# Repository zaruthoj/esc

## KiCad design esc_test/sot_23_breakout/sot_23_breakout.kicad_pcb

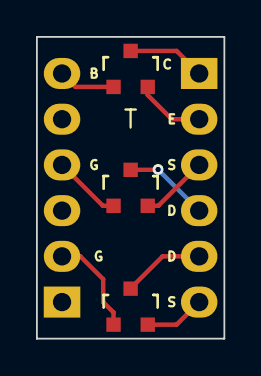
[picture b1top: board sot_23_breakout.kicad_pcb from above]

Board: 2 copper layers, 10.4 x 16.8 mm, 5 parts (0 on the bottom side), 9 nets.

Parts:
P1, P2: CONN_01X06; Pin_Header_Straight_1x06_no_outline
Q1: Q_NPN_BEC; SOT-23
Q2: P; SOT-23
Q3: N; SOT-23

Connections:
unnamed: P1.2, Q3.1
unnamed: P1.4, Q2.1
unnamed: P1.6, Q1.1
unnamed: P2.1, Q1.3
unnamed: P2.2, Q1.2
unnamed: P2.3, Q2.2
unnamed: P2.4, Q2.3
unnamed: P2.5, Q3.3
unnamed: P2.6, Q3.2

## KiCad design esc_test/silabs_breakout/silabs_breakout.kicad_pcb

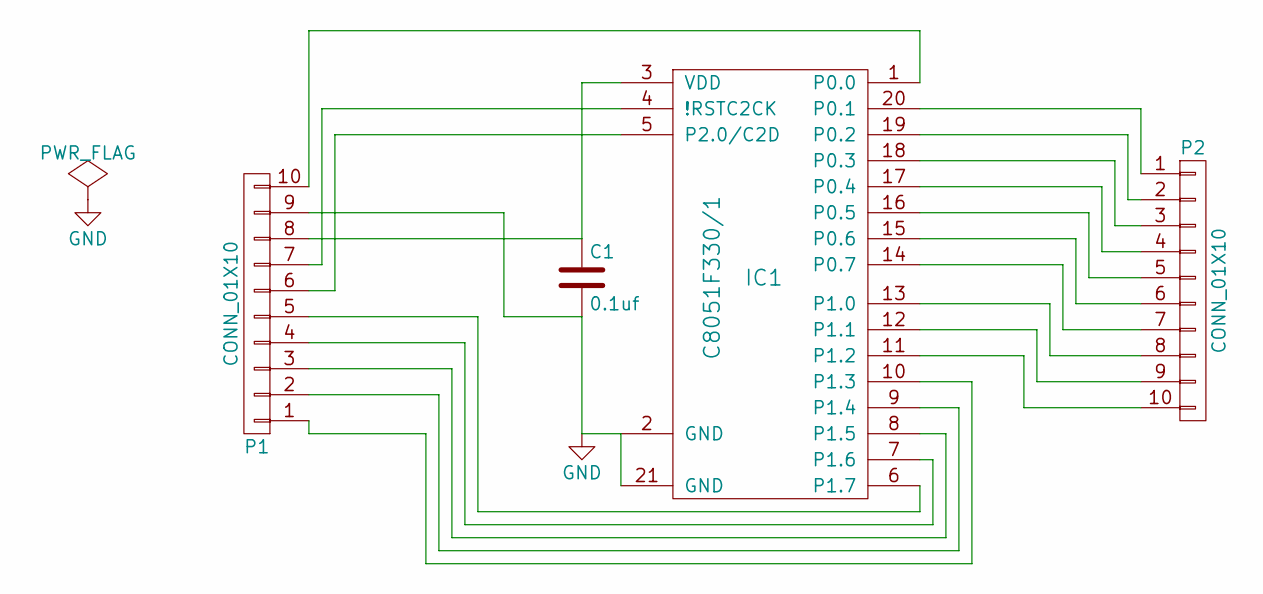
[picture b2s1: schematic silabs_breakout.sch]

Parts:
C1: 0.1uf; C_0805
IC1: C8051F330/1; QFN-20-1EP_4x4mm_Pitch0.5mm
P1, P2: CONN_01X10; Pin_Header_Straight_1x10

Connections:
GND: C1.2, IC1.2 (GND), IC1.21 (GND), P1.9
unnamed: C1.1, IC1.3 (VDD), P1.8
unnamed: IC1.1 (P0.0), P1.10
unnamed: IC1.4 (!RSTC2CK), P1.7
unnamed: IC1.5 (P2.0/C2D), P1.6
unnamed: IC1.6 (P1.7), P1.5
unnamed: IC1.7 (P1.6), P1.4
unnamed: IC1.8 (P1.5), P1.3
unnamed: IC1.9 (P1.4), P1.2
unnamed: IC1.10 (P1.3), P1.1
unnamed: IC1.11 (P1.2), P2.10
unnamed: IC1.12 (P1.1), P2.9
unnamed: IC1.13 (P1.0), P2.8
unnamed: IC1.14 (P0.7), P2.7
unnamed: IC1.15 (P0.6), P2.6
unnamed: IC1.16 (P0.5), P2.5
unnamed: IC1.17 (P0.4), P2.4
unnamed: IC1.18 (P0.3), P2.3
unnamed: IC1.19 (P0.2), P2.2
unnamed: IC1.20 (P0.1), P2.1

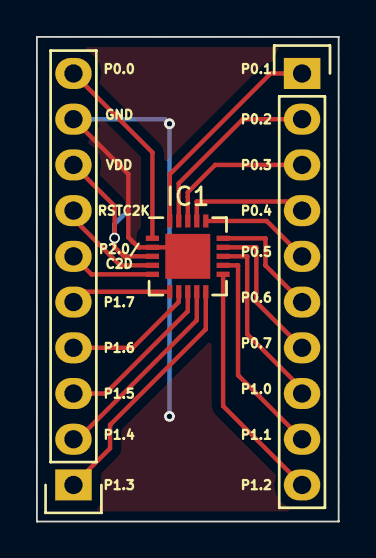
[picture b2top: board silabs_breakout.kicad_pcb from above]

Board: 2 copper layers, 16.8 x 26.9 mm, 4 parts (1 on the bottom side), 20 nets.

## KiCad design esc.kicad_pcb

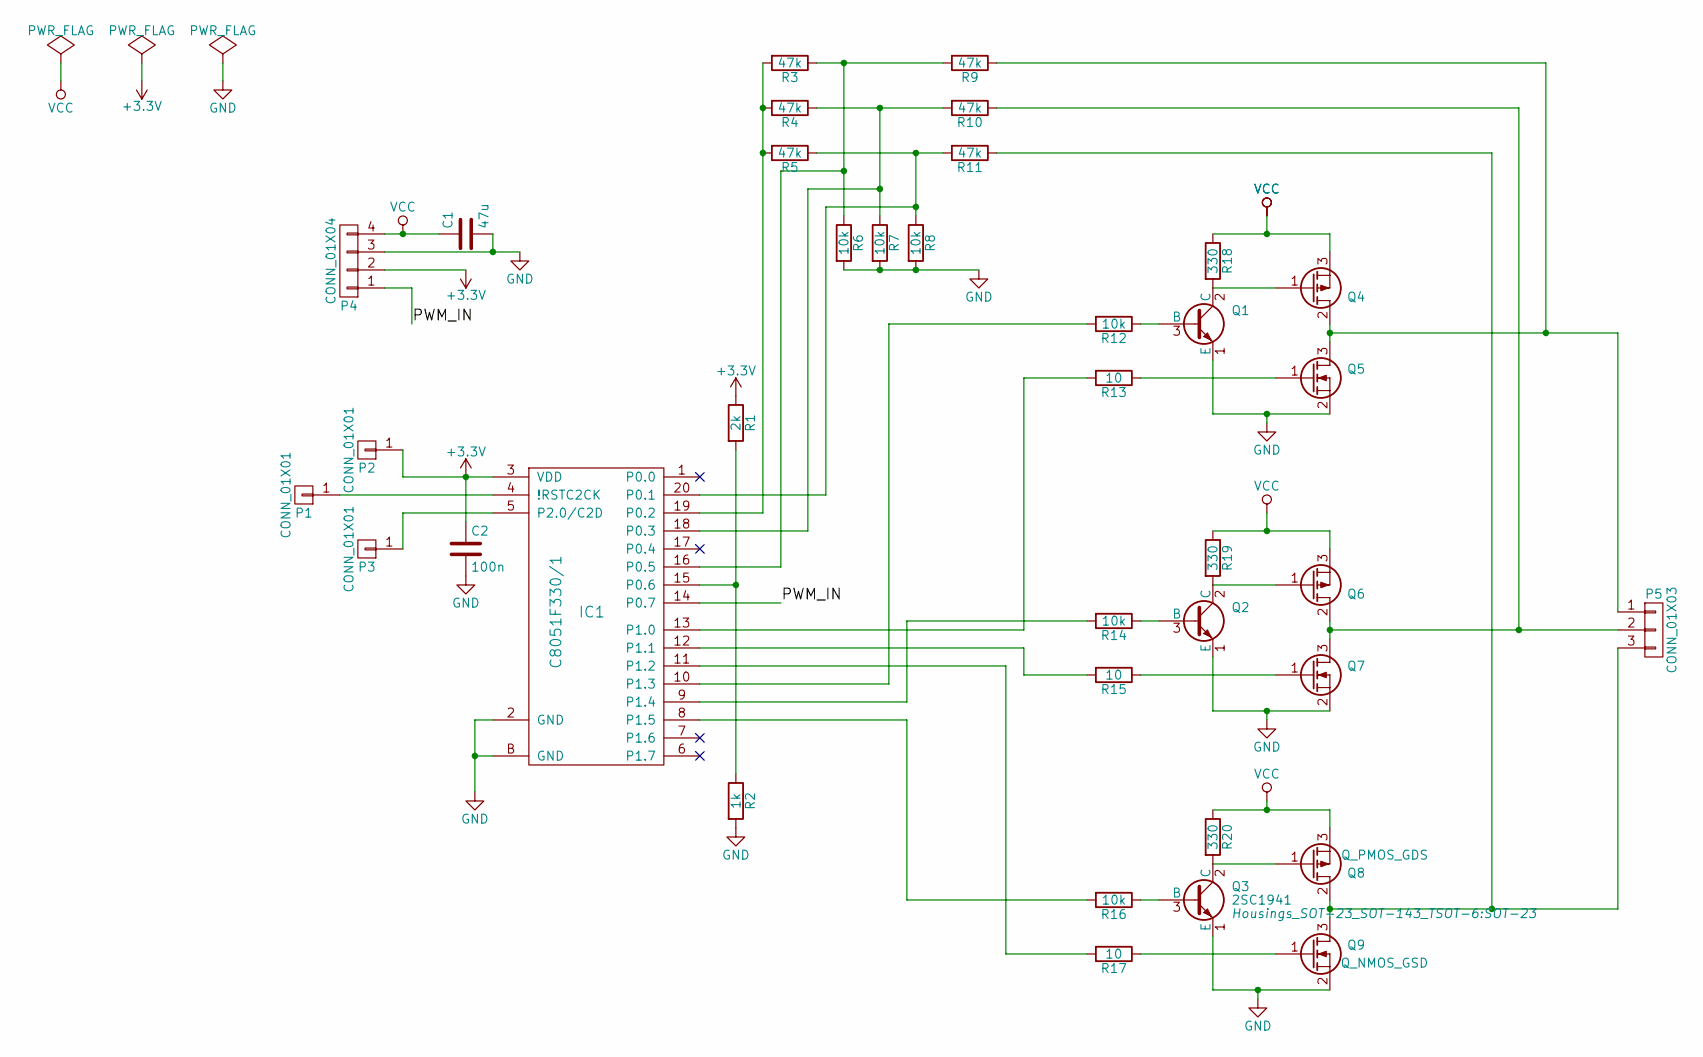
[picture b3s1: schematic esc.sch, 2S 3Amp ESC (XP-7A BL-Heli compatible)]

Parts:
C1: 47u; C_1210
C2: 100n; C_0402
IC1: C8051F330/1; QFN-20-1EP_4x4mm_Pitch0.5mm
P1, P2, P3: CONN_01X01
P4: CONN_01X04
P5: CONN_01X03
Q1, Q2, Q3: 2SC1941; SOT-23
Q4, Q6, Q8: Q_PMOS_GDS; SOT-23
Q5, Q7, Q9: Q_NMOS_GSD; SOT-23
R1: 2k; R_0402
R2: 1k; R_0402
R3, R4, R5, R9, R10, R11: 47k; R_0402
R6, R7, R8, R12, R14, R16: 10k; R_0402
R13, R15, R17: 10; R_0402
R18, R19, R20: 330; R_0402

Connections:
+3V3: C2.1, IC1.3 (VDD), P2.1, P4.2, R1.1
/PWM_IN: IC1.14 (P0.7), P4.1
GND: C1.2, C2.2, IC1.2 (GND), IC1.21 (GND), IC1.B (GND), P4.3, Q1.1 (E), Q2.1 (E), Q3.1 (E), Q5.2 (S), Q7.2 (S), Q9.2 (S), R2.2, R6.2, R7.2, R8.2
unnamed: IC1.4 (!RSTC2CK), P1.1
unnamed: IC1.5 (P2.0/C2D), P3.1
unnamed: IC1.8 (P1.5), R16.2
unnamed: IC1.9 (P1.4), R14.2
unnamed: IC1.10 (P1.3), R12.2
unnamed: IC1.11 (P1.2), R17.2
unnamed: IC1.12 (P1.1), R15.2
unnamed: IC1.13 (P1.0), R13.2
unnamed: IC1.15 (P0.6), R1.2, R2.1
unnamed: IC1.16 (P0.5), R3.1, R6.1, R9.2
unnamed: IC1.18 (P0.3), R4.1, R7.1, R10.2
unnamed: IC1.19 (P0.2), R3.2, R4.2, R5.2
unnamed: IC1.20 (P0.1), R5.1, R8.1, R11.2
unnamed: P5.1, Q4.2 (D), Q5.3 (D), R9.1
unnamed: P5.2, Q6.2 (D), Q7.3 (D), R10.1
unnamed: P5.3, Q8.2 (D), Q9.3 (D), R11.1
unnamed: Q1.2 (C), Q4.1 (G), R18.2
unnamed: Q1.3 (B), R12.1
unnamed: Q2.2 (C), Q6.1 (G), R19.2
unnamed: Q2.3 (B), R14.1
unnamed: Q3.2 (C), Q8.1 (G), R20.2
unnamed: Q3.3 (B), R16.1
unnamed: Q5.1 (G), R13.1
unnamed: Q7.1 (G), R15.1
unnamed: Q9.1 (G), R17.1
VCC: C1.1, P4.4, Q4.3 (S), Q6.3 (S), Q8.3 (S), R18.1, R19.1, R20.1

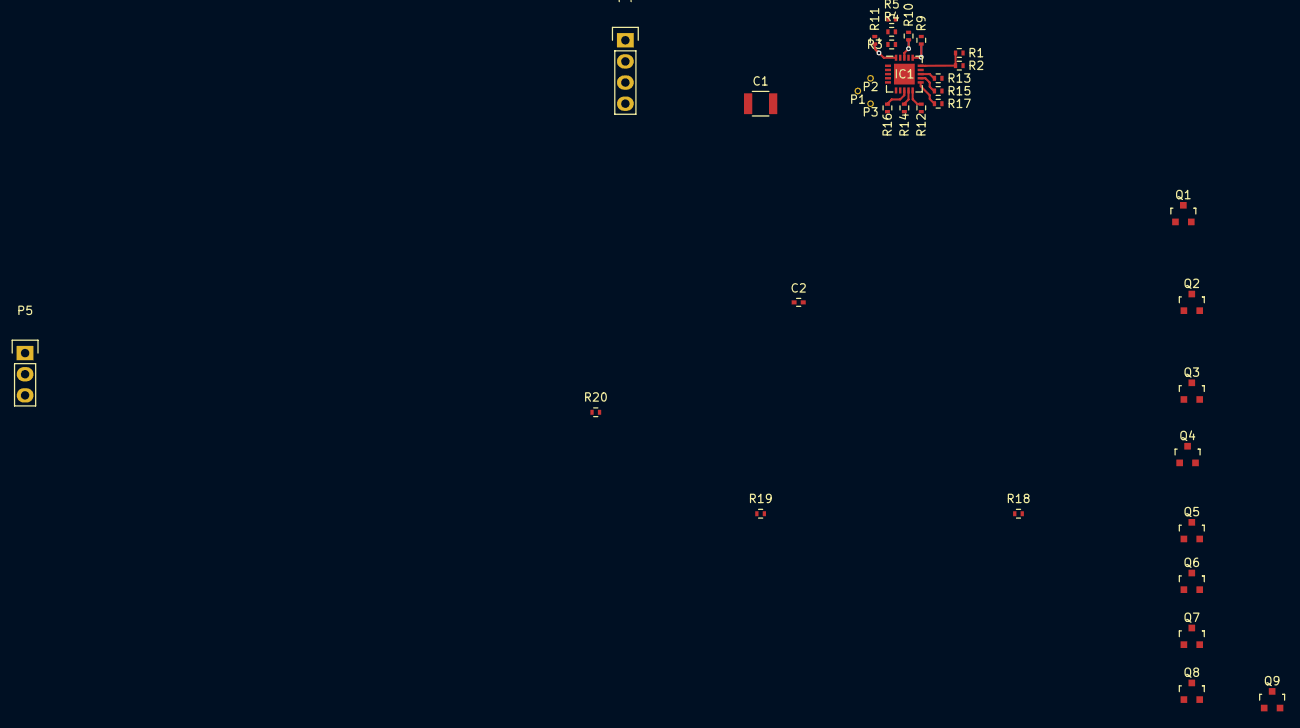
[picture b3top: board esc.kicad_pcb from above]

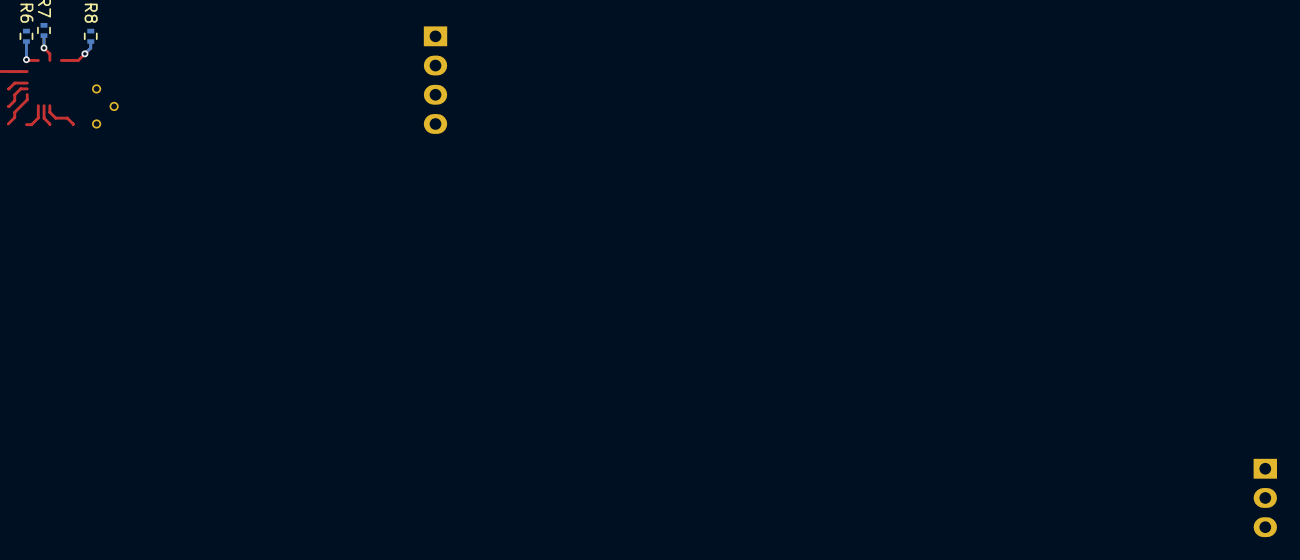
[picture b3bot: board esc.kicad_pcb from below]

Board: 2 copper layers, 37 parts (3 on the bottom side), 29 nets.

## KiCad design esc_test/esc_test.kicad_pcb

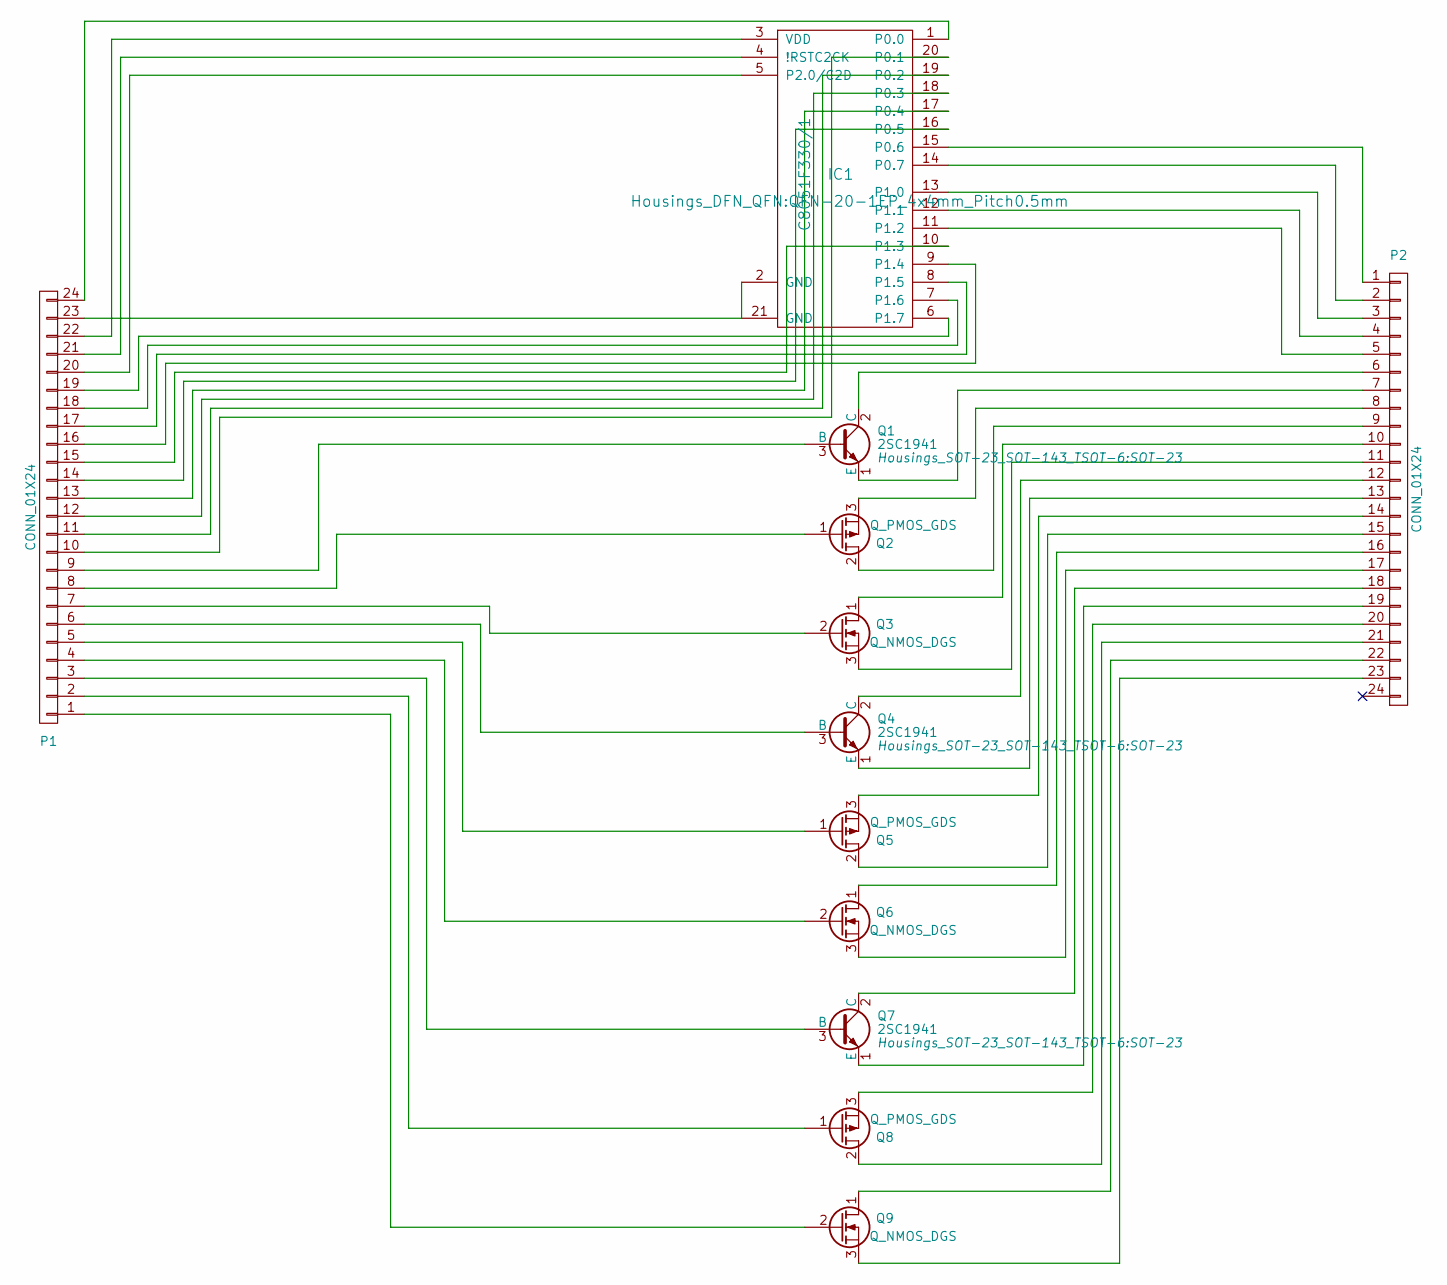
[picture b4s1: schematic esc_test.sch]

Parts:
IC1: C8051F330/1; QFN-20-1EP_4x4mm_Pitch0.5mm
P1, P2: CONN_01X24; Socket_Strip_Straight_1x24
Q1, Q4, Q7: 2SC1941; SOT-23
Q2, Q5, Q8: Q_PMOS_GDS; SOT-23
Q3, Q6, Q9: Q_NMOS_DGS; SOT-23

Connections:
unnamed: IC1.1 (P0.0), P1.24
unnamed: IC1.2 (GND), IC1.21 (GND), P1.23
unnamed: IC1.3 (VDD), P1.22
unnamed: IC1.4 (!RSTC2CK), P1.21
unnamed: IC1.5 (P2.0/C2D), P1.20
unnamed: IC1.6 (P1.7), P1.19
unnamed: IC1.7 (P1.6), P1.18
unnamed: IC1.8 (P1.5), P1.17
unnamed: IC1.9 (P1.4), P1.16
unnamed: IC1.10 (P1.3), P1.15
unnamed: IC1.11 (P1.2), P2.5
unnamed: IC1.12 (P1.1), P2.4
unnamed: IC1.13 (P1.0), P2.3
unnamed: IC1.14 (P0.7), P2.2
unnamed: IC1.15 (P0.6), P2.1
unnamed: IC1.16 (P0.5), P1.14
unnamed: IC1.17 (P0.4), P1.13
unnamed: IC1.18 (P0.3), P1.12
unnamed: IC1.19 (P0.2), P1.11
unnamed: IC1.20 (P0.1), P1.10
unnamed: P1.1, Q9.2 (G)
unnamed: P1.2, Q8.1 (G)
unnamed: P1.3, Q7.3 (B)
unnamed: P1.4, Q6.2 (G)
unnamed: P1.5, Q5.1 (G)
unnamed: P1.6, Q4.3 (B)
unnamed: P1.7, Q3.2 (G)
unnamed: P1.8, Q2.1 (G)
unnamed: P1.9, Q1.3 (B)
unnamed: P2.6, Q1.2 (C)
unnamed: P2.7, Q1.1 (E)
unnamed: P2.8, Q2.3 (S)
unnamed: P2.9, Q2.2 (D)
unnamed: P2.10, Q3.1 (D)
unnamed: P2.11, Q3.3 (S)
unnamed: P2.12, Q4.2 (C)
unnamed: P2.13, Q4.1 (E)
unnamed: P2.14, Q5.3 (S)
unnamed: P2.15, Q5.2 (D)
unnamed: P2.16, Q6.1 (D)
unnamed: P2.17, Q6.3 (S)
unnamed: P2.18, Q7.2 (C)
unnamed: P2.19, Q7.1 (E)
unnamed: P2.20, Q8.3 (S)
unnamed: P2.21, Q8.2 (D)
unnamed: P2.22, Q9.1 (D)
unnamed: P2.23, Q9.3 (S)

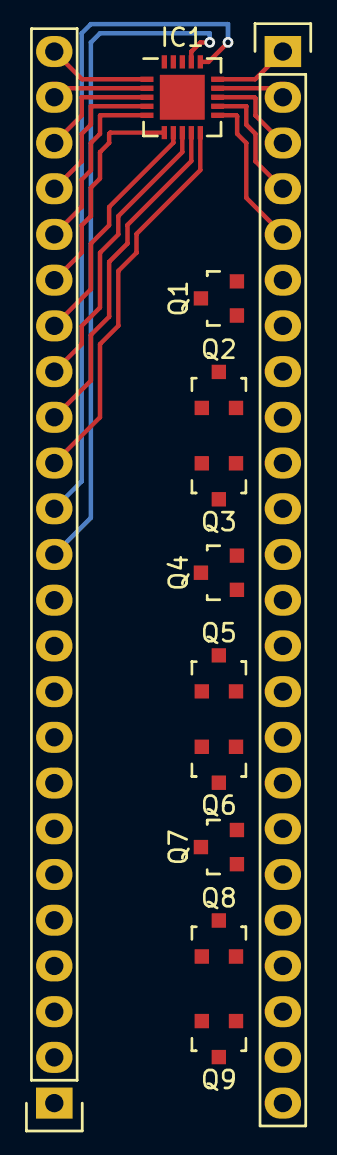
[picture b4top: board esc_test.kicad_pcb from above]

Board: 2 copper layers, 12 parts (0 on the bottom side), 47 nets.

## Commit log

2015-06-23 Initial schematic
2015-06-24 Beginning layout, breadboard test board, and BOM
2015-06-24 Missed some file saves in last commit
2015-06-25 Testing breakouts for SMT chips.
2015-06-28 Final test breakout boards sent to Oshpark.
